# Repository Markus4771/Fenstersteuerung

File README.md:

# Fenstersteuerung

Modulare ESP32-S3-basierte Fenster-/Rollladensteuerung mit 230-V-Rollladenansteuerung, Reedkontakten, RS485 und zwei ULN2003-Ausgangsgruppen.

## Aktueller Hauptplatinenstand

**v3.3ebs2**

Datei:

`hardware/Hauptplatine/Hauptplatine_v3.3ebs2_library_clean_usb_clearance_150x90.kicad_pcb`

### DRC-Status

Der aktuelle KiCad-DRC ist elektrisch sauber:

- 0 offene Verbindungen
- 0 Kurzschlüsse
- 0 Leiterbahnkreuzungen
- 0 Clearance-Fehler
- 0 Dangling-Tracks
- 0 Silkscreen-Warnungen
- 0 Footprint-Fehler

Es verbleiben nur 30 Bibliothekswarnungen durch angepasste bzw. lokal fehlende Footprint-Bibliotheken.

## Hauptfunktionen

- ESP32-S3 DevKitC-1
- 2 × Finder 40.52, 5-V-Spule, DPDT
- Hardware-Interlock für Rollladen AUF/AB
- Mean Well IRM-20-5
- AMS1117-3.3 mit 22-µF-Ausgangskondensator
- MAX3485 RS485
- 2 × ULN2003A
- 2 × 28BYJ-48-Ausgangsgruppe
- Reedkontakte für Offen/Gekippt
- 230-V-Motoranschluss
- getrennte 230-V- und SELV-Bereiche

## Wichtige Dateien

- PCB: `hardware/Hauptplatine/Hauptplatine_v3.3ebs2_library_clean_usb_clearance_150x90.kicad_pcb`
- DRC-Regeln: `hardware/Hauptplatine/Hauptplatine.kicad_dru`
- 230-V-Prüfung: `hardware/Hauptplatine/230V-SICHERHEITSPRUEFUNG.md`
- BOM: `bom/Hauptplatine_v3.3ebs2_BOM.csv`
- Entwicklungsarchiv: `hardware/Hauptplatine/archive/`
- Historie: `docs/ENTWICKLUNGSHISTORIE.md`
- Übergabe für neuen Chat: `NEUER-CHAT.md`

## Noch vor der Prototypenbestellung

1. BOM gegen tatsächlich bestellte Bauteile prüfen.
2. Gerber- und Drill-Dateien aus KiCad erzeugen.
3. Gerber im Viewer kontrollieren.
4. 230-V-Sicherheitsprüfung final abschließen.
5. Erste Inbetriebnahme zunächst ohne Netzspannung durchführen.

## Sicherheit

Der saubere KiCad-DRC ist keine formale Freigabe für 230-V-Betrieb. Luft-/Kriechstrecken, PE-Führung, Absicherung, Bauteilzulassungen, Gehäuse und Endanwendung müssen separat geprüft werden.

## Update v3.3ebs2

- elektrisch sauberer v3.3ebq2-Stand übernommen
- RS485-Klemme bleibt unten, USB-C frei zugänglich
- alle 17 verwendeten Footprints auf projektlokale Bibliothek `Fenstersteuerung.pretty` umgestellt
- `fp-lib-table` liegt im Hauptplatinen-Ordner
- gegenüber v3.3ebq2 keine Änderungen an Routing, Pads, Vias oder Kupfer
- nächster Schritt: KiCad öffnen, Zonen neu füllen und DRC ausführen

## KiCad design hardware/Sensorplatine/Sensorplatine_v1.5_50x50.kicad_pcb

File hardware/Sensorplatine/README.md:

# Sensorplatine

## Status

Aktueller Entwicklungsstand: **v4.0.ac**. Diese Version ist der aktuelle manuell platzierte KiCad-10-Basisstand ohne Leiterbahnen und Vias.

Die Sensorplatine ist als abgesetzte Raumklima- und Anwesenheitssensorplatine für die Fenstersteuerung vorgesehen. Die Reedkontakte für Fenster offen/gekippt bleiben direkt an der Hauptplatine und gehören ausdrücklich **nicht** auf diese Sensorplatine.

## Geplante Messgrößen und Bausteine

| Messgröße | Vorgesehener Baustein | Schnittstelle | Hinweis |
|---|---|---|---|
| Temperatur | BME280 | I²C | gemeinsamer Sensor mit Feuchte und Luftdruck |
| Luftfeuchtigkeit | BME280 | I²C | ±3 % rF typischer Einsatzbereich laut Hersteller |
| Luftdruck | BME280 | I²C | 300…1100 hPa |
| CO₂ | Sensirion SCD41 | I²C | echter CO₂-Sensor, spezifizierter Bereich 400…5000 ppm |
| VOC / Luftqualität | Sensirion SGP40 | I²C | VOC-Index für Lüftungs-/Luftgütelogik |
| Helligkeit | Vishay VEML7700 | I²C | digitaler Umgebungslichtsensor |
| Bewegung / Anwesenheit | modular | GPIO / UART | PIR oder mmWave-Modul; endgültiger Typ noch festzulegen |
| Schallpegel | digitales MEMS-Mikrofon | I²S | z. B. INMP441-Klasse; relative Geräuschpegelmessung, keine normgerechte Schallpegelmessung |

## Architektur

Ziel ist, möglichst viele Sensoren über **I²C** anzubinden. Dadurch benötigen BME280, SCD41, SGP40 und VEML7700 gemeinsam nur SDA und SCL.

Zusätzlich werden benötigt:

- I²S-Leitungen für das digitale MEMS-Mikrofon
- mindestens ein GPIO für einen PIR-Sensor
- optional UART für ein mmWave-Anwesenheitsmodul
- Versorgung 3,3 V und ggf. 5 V
- GND

## Bewegung / Anwesenheit

Die Platine soll so vorbereitet werden, dass entweder:

1. ein einfacher PIR-Bewegungssensor verwendet werden kann, oder
2. ein mmWave-Anwesenheitssensor über einen Steckverbinder angeschlossen werden kann.

mmWave ist besonders interessant, weil damit auch ruhende Personen erkannt werden können. Wegen Baugröße und unterschiedlicher Modulvarianten soll der mmWave-Sensor zunächst nicht fest als SMD-Bauteil auf die Platine gesetzt werden.

## Schallpegel

Die Schallmessung soll mit einem digitalen MEMS-Mikrofon erfolgen.

Ziel:

- relativer Geräuschpegel
- Erkennung von ungewöhnlich hoher Lautstärke
- Verlauf über die Zeit
- mögliche spätere Nutzung für Anwesenheits-/Komfortlogik

Die Platine ist **nicht** als kalibriertes oder normgerechtes Schallpegelmessgerät vorgesehen.

## Mechanik / Layout

Beim späteren PCB-Layout beachten:

- BME280 möglichst weit von Spannungsreglern, ESP32 und anderen Wärmequellen platzieren
- SCD41 mit freiem Luftaustausch montieren
- SGP40 ebenfalls mit gutem Luftaustausch platzieren
- VEML7700 an einer Gehäuseöffnung bzw. lichtdurchlässigen Stelle platzieren
- Mikrofon mit definierter Schallöffnung im Gehäuse
- Sensorbereiche nicht unnötig durch Kupferflächen oder Wärmequellen aufheizen
- Befestigungsbohrungen vorsehen
- Beschriftung der Steckverbinder auf dem Silkscreen

## Noch festzulegen

1. Verbindung zwischen Hauptplatine und Sensorplatine
2. Kabellänge zwischen beiden Platinen
3. Versorgungsspannung(en) der Sensorplatine
4. PIR- und/oder mmWave-Modultyp
5. endgültiger MEMS-Mikrofontyp
6. Gehäuseabmessungen und Position der Luft-/Licht-/Schallöffnungen
7. Schutzbeschaltung für die Verbindung zur Hauptplatine
8. KiCad-Schaltplan und PCB-Version v1.0

## Schaltplanstand v1.0

Aktiver Entwurf:

- `Sensorplatine_v1.0.sch`
- lokale Symbolbibliothek: `Sensorplatine_v1.0-cache.lib`
- Pinbelegung: `PINBELEGUNG_v1.0.csv`
- Schaltplan-Spezifikation: `SCHALTPLAN_v1.0.md`

Der Schaltplan enthält bereits:

- STM32G031K8T6 (LQFP-32)
- AP2112K-3.3
- MAX3485 / RS485
- BME280
- SCD41
- SGP40
- VEML7700
- HLK-LD2450
- I2S-MEMS-Mikrofon als noch zu finalisierender Typ
- 4-poligen Anschluss zur Hauptplatine
- SWD-Programmieranschluss

### Vor PCB-Layout noch final festzulegen

1. konkreter I2S-MEMS-Mikrofontyp und Footprint
2. RS485-TVS-Typ
3. 120-Ohm-Abschluss als Jumper/Lötbrücke
4. endgültiger 4-poliger Steckverbinder
5. Footprint des HLK-LD2450 und Antennen-Keepout
6. mechanische Positionen innerhalb 50 x 50 mm

## PCB-Placement v1.0

Erster mechanischer 50 x 50 mm Placement-Entwurf:

`Sensorplatine_v1.0_placement_50x50.kicad_pcb`

Aktuelle Platzierung:

- HLK-LD2450 entlang der oberen Platinenkante
- definierter Antennen-Keepout an der Oberkante
- SCD41 links mit eigener Luftzone
- BME280 und SGP40 mittig im Sensorbereich
- VEML7700 am rechten Rand
- STM32G031K8T6 zentral unten
- MAX3485 und SM712 nahe RS485-Seite
- AP2112K-3.3 unten rechts
- T5848 nahe Gehäuserand für Schallöffnung
- JST-XH 4-polig unten links
- SWD-Header unten
- zunächst zwei 2.5-mm-Befestigungsbohrungen unten

Dieser Stand ist absichtlich noch nicht geroutet. Vor dem Routing werden Footprints und mechanische Abstände final geprüft.

## Routing-Stand v1.0

Neue Datei:

`Sensorplatine_v1.0_routing_draft_50x50.kicad_pcb`

Bereits elektrisch geroutet:

- 5-V-Eingang vom JST-XH-Stecker zum AP2112K
- 3,3-V-Versorgung vom AP2112K zum STM32 und MAX3485
- GND-Verbindungen im Kernbereich
- RS485 A/B vom Hauptanschluss über SM712 zum MAX3485
- USART-Verbindungen MAX3485 <-> STM32
- DE/RE-Steuerung MAX3485 <-> STM32

Die Sensor-Footprints sind in diesem Stand noch bewusst als Platzhalter markiert. Vor dem Routing von I2C, I2S und LD2450 werden die exakten Hersteller-Landpatterns übernommen und geprüft.

## Maximaler Routing-Stand – v1.0

In `Sensorplatine_v1.0_routing_draft_50x50.kicad_pcb` sind jetzt zusätzlich geroutet:

- I2C SDA/SCL vom STM32 bis in die zentrale Sensorzone
- UART TX/RX vom STM32 bis zur LD2450-Modulschnittstelle
- 5 V und GND bis zur LD2450-Modulschnittstelle
- I2S WS / CK / SD vom STM32 bis zur Mikrofonzone
- SWDIO / SWCLK / NRST / 3V3 / GND bis zum SWD-Header

Damit sind praktisch alle langen bzw. kritischen Leiterbahnstrecken vorgeroutet.

Noch offen bleiben nur die kurzen lokalen Verbindungen direkt an:

- BME280
- SCD41
- SGP40
- VEML7700
- T5848
- endgültiges LD2450-Landpattern

Grund: Für diese Bauteile werden vor einer fertigungstauglichen Version die exakten Hersteller-Landpatterns übernommen. Die derzeitigen Sensorflächen sind ausdrücklich noch Platzhalter.

Der aktuelle Stand ist daher ein **maximal gerouteter mechanisch-elektrischer Entwurf**, aber noch keine freigegebene Fertigungsdatei. Vor Gerber-Erzeugung müssen die finalen Footprints eingesetzt und ein KiCad-DRC durchgeführt werden.

## Versionierung

Ab jetzt wird die Sensorplatine strikt versionsbasiert weiterentwickelt.

Regeln:

- vorhandene Hardwareversionen werden nicht mehr überschrieben
- jede elektrische oder mechanische Änderung erzeugt eine neue Version
- reine Dokumentationskorrekturen können innerhalb derselben Version dokumentiert werden
- DRC-Berichte werden passend zur jeweiligen Version abgelegt
- Gerber-Dateien erhalten immer dieselbe Versionsnummer wie das zugehörige PCB

Aktueller Stand:

- **v1.0** = erster 50 x 50 mm Sensorplatinen-Entwurf mit STM32G031, RS485, LD2450 und vorgerouteten Sensorbussen
- nächste Entwicklungsstufe: **v1.1**

Geplante Dateinamen:

- `Sensorplatine_v1.0_routing_draft_50x50.kicad_pcb` – eingefrorener aktueller Stand
- `Sensorplatine_v1.1_50x50.kicad_pcb` – nächste bearbeitete PCB-Version
- `DRC_v1.0.rpt`, `DRC_v1.1.rpt` usw.
- spätere Gerber: `Sensorplatine_v1.1_Gerber.zip` usw.

## Version v1.2

Datei:

`Sensorplatine_v1.2_50x50.kicad_pcb`

Änderungen gegenüber v1.1:

- 5-V-Versorgung neu geroutet
- GND-Backbone neu aufgebaut
- 3,3-V-Verteilung neu geroutet
- RS485 A/B getrennt geführt
- MAX3485 <-> STM32 neu geroutet
- I2C bis zur Sensorzone geroutet
- LD2450 UART sowie 5 V/GND bis zur Modulschnittstelle geroutet
- I2S bis zur Mikrofonzone geroutet
- SWD neu geroutet
- SWD-Header weiter in die Platinenkontur verschoben

Hinweis:
v1.2 basiert auf der in GitHub gespeicherten v1.1. Lokal in KiCad verschobene Bauteile aus einer nicht hochgeladenen `.kicad_pcb` konnten noch nicht übernommen werden.

## Version 4.0

### v4.0.aa – manuelle Neuplatzierung

Datei:

`Sensorplatine_v4.0.aa_placement_only_50x50.kicad_pcb`

- neue manuelle Bauteilplatzierung
- KiCad-10-Dateiformat
- keine Leiterbahnen
- keine Vias
- dient als saubere mechanische Ausgangsbasis

### v4.0.ab – Routingversuch

Datei:

`Sensorplatine_v4.0.ab_50x50.kicad_pcb`

DRC:

`DRC_v4.0.ab.rpt`

Dieser Stand war ein maximaler 2-Lagen-Routingversuch. Der DRC zeigte zu viele geometrische Konflikte und Kurzschlüsse. **v4.0.ab ist deshalb ausdrücklich nicht für Fertigung oder weitere Entwicklung freigegeben.**

### v4.0.ac – aktueller Basisstand

Datei:

`Sensorplatine_v4.0.ac_50x50.kicad_pcb`

- basiert auf der aktuellen manuellen Bauteilplatzierung
- KiCad 10
- aktuell 0 Leiterbahnsegmente
- aktuell 0 Vias
- neuer Ausgangspunkt für das nächste kontrollierte Routing
- Bauteilpositionen sollen vor dem nächsten Routing nicht automatisch verändert werden

**Aktueller Arbeitsstand: v4.0.ae**

### v4.0.ad – konservatives Kernrouting

Datei:

`Sensorplatine_v4.0.ad_50x50.kicad_pcb`

- basiert auf v4.0.ac
- manuelle Bauteilplatzierung unverändert
- +5 V und GND im Kernbereich geroutet
- RS485_A und RS485_B geroutet
- D1 und U7 im RS485-Pfad berücksichtigt
- +3V3 von U9 zu U7 geroutet
- enge Sensor-, I2C-, I2S- und SWD-Bereiche noch bewusst offen
- vor Weiterentwicklung ist ein neuer KiCad-DRC erforderlich

**Aktueller Arbeitsstand: v4.0.ad**

### v4.0.ae – RS485-only routing

Datei:

`Sensorplatine_v4.0.ae_50x50.kicad_pcb`

- basiert auf der reinen v4.0.aa-Manuellplatzierung
- nur RS485_A und RS485_B geroutet
- D1 und U7 angebunden
- Versorgung, I2C, I2S und SWD bleiben bewusst offen
- Ziel: zuerst einen DRC-sauberen RS485-Kern herstellen

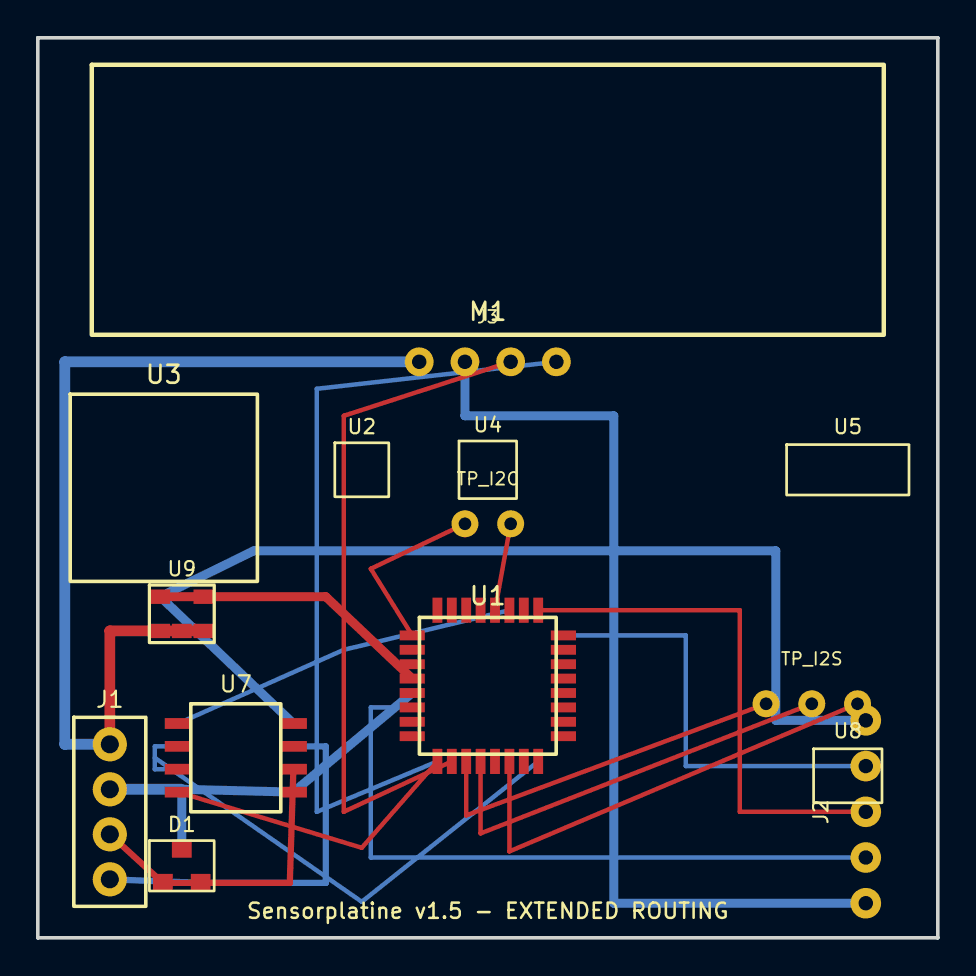
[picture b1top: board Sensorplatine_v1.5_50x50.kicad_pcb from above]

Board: 2 copper layers, 50.0 x 50.0 mm, 15 parts (0 on the bottom side), 18 nets.

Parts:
D1: SM712; SM712_SOT23
J1: 5V/GND/A/B; JST_XH_1x04
J2: SWD; SWD_1x05
J3: LD2450 temporary interface; LD2450_IF
M1: HLK-LD2450; HLK_LD2450
TP_I2C: I2C trunk to sensor zone; I2C_TEMP_TERMINALS
TP_I2S: I2S trunk to microphone zone; I2S_TEMP_TERMINALS
U1: STM32G031K8T6; STM32G031K8T6_LQFP32
U2: BME280 - LANDPATTERN TODO; BME280_PLACEHOLDER
U3: SCD41 - LANDPATTERN TODO; SCD41_PLACEHOLDER
U4: SGP40 - LANDPATTERN TODO; SGP40_PLACEHOLDER
U5: VEML7700 - LANDPATTERN TODO; VEML7700_PLACEHOLDER
U7: MAX3485; MAX3485_SOIC8
U8: T5848 - LANDPATTERN TODO; T5848_PLACEHOLDER
U9: AP2112K-3.3; AP2112K_SOT23-5

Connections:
+3V3: J2.1, U1.4, U7.8, U9.5
+5V: J1.1, J3.1, U9.1, U9.3
GND: D1.3, J1.2, J2.5, J3.2, U1.5, U7.5, U9.2
I2C_SCL: TP_I2C.2, U1.28
I2C_SDA: TP_I2C.1, U1.1
I2S_CK: TP_I2S.2, U1.12
I2S_SD: TP_I2S.3, U1.14
I2S_WS: TP_I2S.1, U1.11
LD2450_RX: J3.4, U1.9
LD2450_TX: J3.3, U1.10
NRST: J2.4, U1.6
RS485_A: D1.1, J1.3, U7.6
RS485_B: D1.2, J1.4, U7.7
RS485_DE: U1.16, U7.2, U7.3
RS485_RX: U1.27, U7.1
RS485_TX: U1.32, U7.4
SWCLK: J2.3, U1.25
SWDIO: J2.2, U1.24

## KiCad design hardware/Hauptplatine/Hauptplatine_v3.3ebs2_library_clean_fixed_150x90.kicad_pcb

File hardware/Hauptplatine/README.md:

# Hauptplatine – KiCad-Projektordner

## Wichtig beim Öffnen

Nicht nur die einzelne `.kicad_pcb`-Datei herunterladen.

Für die projektlokale Footprint-Bibliothek müssen diese Dateien/Ordner zusammen bleiben:

- `Hauptplatine_v3.3ebs2_library_clean_fixed_150x90.kicad_pcb`
- `fp-lib-table`
- `Fenstersteuerung.pretty/`
- `Hauptplatine.kicad_dru`

Am einfachsten:

1. komplettes Repository herunterladen/klonen
2. in `hardware/Hauptplatine/` wechseln
3. `Hauptplatine_v3.3ebs2_library_clean_fixed_150x90.kicad_pcb` aus diesem Ordner öffnen

Die `fp-lib-table` verweist auf:

`${KIPRJMOD}/Fenstersteuerung.pretty`

Wenn nur die PCB-Datei separat heruntergeladen wird, kann KiCad die lokale Bibliothek nicht finden und meldet für alle Footprints:

`Die aktuelle Konfiguration enthält die Footprint-Bibliothek "Fenstersteuerung" nicht`

## Aktueller DRC-Stand

DRCebs.rpt vom 2026-09-29:

- 0 unconnected pads
- 0 Footprint errors
- keine elektrischen DRC-Fehler
- 30 reine Library-Warnungen wegen nicht geladener Projektbibliothek

Nach Öffnen aus dem vollständigen Projektordner bitte Zonen neu füllen und DRC erneut ausführen.

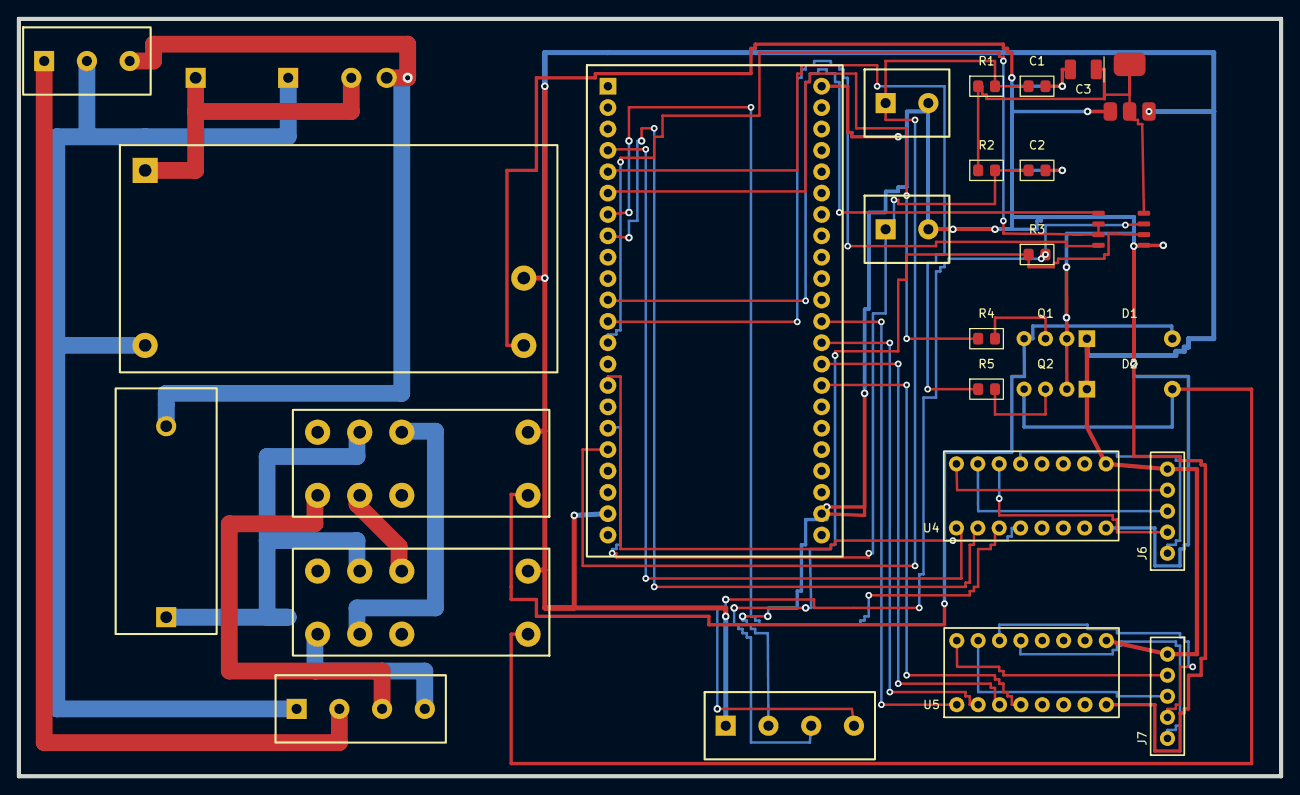
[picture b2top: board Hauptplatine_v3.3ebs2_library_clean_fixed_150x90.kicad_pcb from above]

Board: 2 copper layers, 150.0 x 90.0 mm, 30 parts (0 on the bottom side), 41 nets.

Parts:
C1, C2: 100n; C_0805_2012Metric
C3: 22uF 10V TANT; CP_EIA-3528-21_Kemet-B
D1, D2: 1N4007; D_DO-41_SOD81_P10.16mm_Horizontal
F1: T1A; Littelfuse_646_5x20
F2: T2A; Littelfuse_646_5x20
J1: 230V IN L/N/PE; Phoenix_MKDS-1.5_3P_P5.08
J2: REED OFFEN; Phoenix_MKDS-1.5_2P_P5.08
J3: REED GEKIPPT; Phoenix_MKDS-1.5_2P_P5.08
J4: RS485 5V/GND/A/B; Phoenix_MKDS-1.5_4P_P5.08
J5: MOTOR N/PE/AUF/AB; Phoenix_MKDS-1.5_4P_P5.08
J6: 28BYJ-48 OBEN; JST_XH_B5B-XH-A_1x05_P2.50mm_Vertical
J7: 28BYJ-48 UNTEN; JST_XH_B5B-XH-A_1x05_P2.50mm_Vertical
K1: Finder 40.52.9.005.0000 AUF; Relay_DPDT_Finder_40.52
K2: Finder 40.52.9.005.0000 AB; Relay_DPDT_Finder_40.52
PS1: IRM-20-5; Converter_ACDC_MeanWell_IRM-20-xx_THT
Q1: BC337 AUF; TO-92_Inline_Wide
Q2: BC337 AB; TO-92_Inline_Wide
R1, R2: 10k; R_0805_2012Metric
R3: 120R TERM; R_0805_2012Metric
R4, R5: 470R; R_0805_2012Metric
RV1: MOV 275VAC; MOV_S14K275_P7.5
U1: ESP32-S3 DevKitC-1 headers; ESP32-S3_DevKitC-1_Carrier
U2: AMS1117-3.3; SOT-223-3_TabPin2
U3: MAX3485; SOIC-8_3.9x4.9mm_P1.27mm
U4: ULN2003A OBEN; DIP-16_W7.62mm
U5: ULN2003A UNTEN; DIP-16_W7.62mm

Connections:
/+3V3: C3.1, R1.1, R2.1, U2.2, U3.8
/+5V: D1.1, D2.1, J4.1, J6.5, J7.5, K1.A2, K2.A2, PS1.4 (+Vo), U1.41, U2.3, U4.9, U5.9
/AC_L: F1.2, F2.2, J1.3
/AC_N: J1.2, J5.1, PS1.2 (AC/N), RV1.1
/BOT_COIL_1: J7.4, U5.16
/BOT_COIL_2: J7.3, U5.15
/BOT_COIL_3: J7.2, U5.14
/BOT_COIL_4: J7.1, U5.13
/DN_FEED: K1.22, K2.11
/GND: C1.2, C2.2, C3.2, J2.2, J3.2, J4.2, PS1.3 (-Vo), Q1.3, Q2.3, U1.2, U1.42, U2.1, U3.5, U4.8, U5.8
/K1_COIL_LOW: D1.2, K1.A1, Q1.1
/K2_COIL_LOW: D2.2, K2.A1, Q2.1
/L_MOTOR: F2.1, K1.21, K2.21
/L_PSU_FUSED: F1.1, PS1.1 (AC/L), RV1.2
/MOTOR_DN: J5.4, K2.14
/MOTOR_UP: J5.3, K1.14
/PE: J1.1, J5.2
/Q1_BASE: Q1.2, R4.2
/Q2_BASE: Q2.2, R5.2
/REED_OPEN: C1.1, J2.1, R1.2, U1.35
/REED_TILT: C2.1, J3.1, R2.2, U1.33
/ROLL_DN: R5.1, U1.9
/ROLL_UP: R4.1, U1.11
/RS485_A: J4.3, R3.1, U3.6
/RS485_B: J4.4, R3.2, U3.7
/RS485_DE: U1.25, U3.2, U3.3
/RS485_RX: U1.21, U3.1
/RS485_TX: U1.23, U3.4
/STEP_BOT_1: U1.24, U5.1
/STEP_BOT_2: U1.26, U5.2
/STEP_BOT_3: U1.28, U5.3
/STEP_BOT_4: U1.30, U5.4
/STEP_TOP_1: U1.7, U4.1
/STEP_TOP_2: U1.15, U4.2
/STEP_TOP_3: U1.13, U4.3
/STEP_TOP_4: U1.29, U4.4
/TOP_COIL_1: J6.4, U4.16
/TOP_COIL_2: J6.3, U4.15
/TOP_COIL_3: J6.2, U4.14
/TOP_COIL_4: J6.1, U4.13
/UP_FEED: K1.11, K2.22

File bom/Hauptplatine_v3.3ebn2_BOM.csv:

Qty,References,Value,Footprint,Verification
2,"C1 C2","100n","Capacitor_SMD:C_0805_2012Metric",""
1,"C3","22uF 10V TANT","Capacitor_Tantalum_SMD:CP_EIA-3528-21_Kemet-B","AMS1117 output stabilization capacitor"
2,"D1 D2","1N4007","Diode_THT:D_DO-41_SOD81_P10.16mm_Horizontal",""
1,"F1","T1A","RolladenCustom:Littelfuse_646_5x20","Local/custom footprint - verify against purchased part"
1,"F2","T2A","RolladenCustom:Littelfuse_646_5x20","Local/custom footprint - verify against purchased part"
1,"J1","230V IN L/N/PE","RolladenCustom:Phoenix_MKDS-1.5_3P_P5.08","Local/custom footprint - verify against purchased part"
1,"J2","REED OFFEN","RolladenCustom:Phoenix_MKDS-1.5_2P_P5.08","Local/custom footprint - verify against purchased part"
1,"J3","REED GEKIPPT","RolladenCustom:Phoenix_MKDS-1.5_2P_P5.08","Local/custom footprint - verify against purchased part"
1,"J4","RS485 5V/GND/A/B","RolladenCustom:Phoenix_MKDS-1.5_4P_P5.08","Local/custom footprint - verify against purchased part"
1,"J5","MOTOR N/PE/AUF/AB","RolladenCustom:Phoenix_MKDS-1.5_4P_P5.08","Local/custom footprint - verify against purchased part"
1,"J6","28BYJ-48 OBEN","Connector_JST:JST_XH_B5B-XH-A_1x05_P2.50mm_Vertical",""
1,"J7","28BYJ-48 UNTEN","Connector_JST:JST_XH_B5B-XH-A_1x05_P2.50mm_Vertical",""
1,"K1","Finder 40.52.9.005.0000 AUF","Relay_THT:Relay_DPDT_Finder_40.52","Verified footprint grid against Finder 40.52"
1,"K2","Finder 40.52.9.005.0000 AB","Relay_THT:Relay_DPDT_Finder_40.52","Verified footprint grid against Finder 40.52"
1,"PS1","IRM-20-5","Converter_ACDC:Converter_ACDC_MeanWell_IRM-20-xx_THT","Verified footprint/pin mapping against Mean Well IRM-20-5"
1,"Q1","BC337 AUF","Package_TO_SOT_THT:TO-92_Inline_Wide",""
1,"Q2","BC337 AB","Package_TO_SOT_THT:TO-92_Inline_Wide",""
2,"R1 R2","10k","Resistor_SMD:R_0805_2012Metric",""
1,"R3","120R TERM","Resistor_SMD:R_0805_2012Metric",""
2,"R4 R5","470R","Resistor_SMD:R_0805_2012Metric",""
1,"RV1","MOV 275VAC","RolladenCustom:MOV_S14K275_P7.5","Local/custom footprint - verify against purchased part"
1,"U1","ESP32-S3 DevKitC-1 headers","RolladenCustom:ESP32-S3_DevKitC-1_Carrier","Local/custom footprint - pin mapping corrected for DevKitC-1"
1,"U2","AMS1117-3.3","Package_TO_SOT_SMD:SOT-223-3_TabPin2",""
1,"U3","MAX3485","Package_SO:SOIC-8_3.9x4.9mm_P1.27mm",""
1,"U4","ULN2003A OBEN","Package_DIP:DIP-16_W7.62mm",""
1,"U5","ULN2003A UNTEN","Package_DIP:DIP-16_W7.62mm",""
